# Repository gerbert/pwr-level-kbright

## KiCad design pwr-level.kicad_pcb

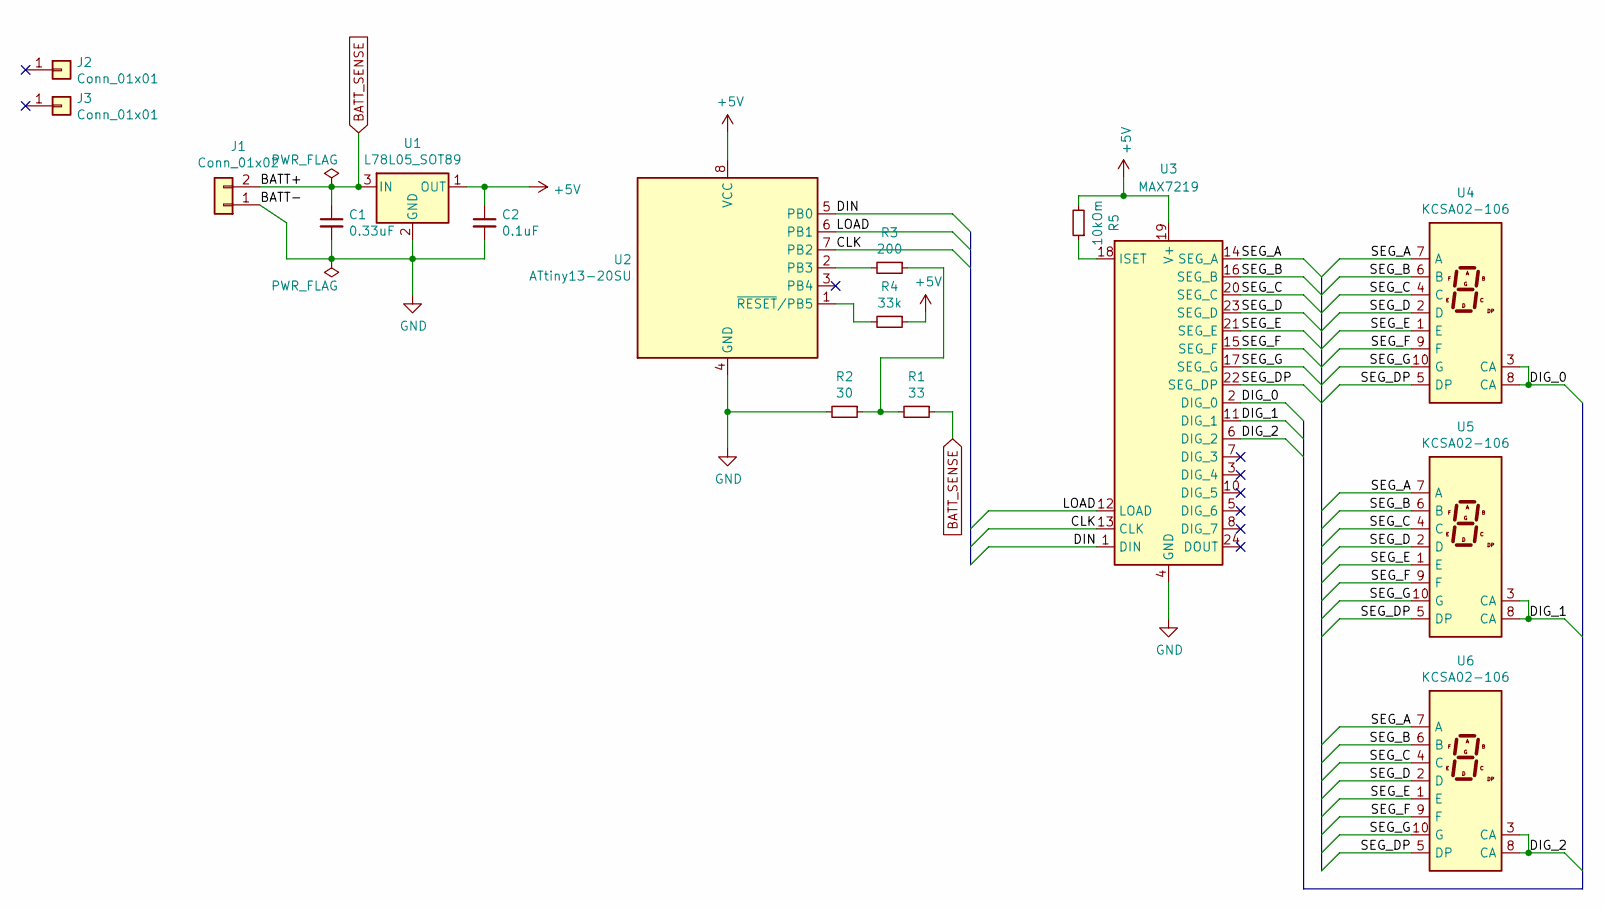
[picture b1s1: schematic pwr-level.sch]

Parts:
C1: 0.33uF; C_1206_3216Metric
C2: 0.1uF; C_1206_3216Metric
J1: Conn_01x02; SolderWirePad_1x02_P3.81mm_Drill0.8mm
J2, J3: Conn_01x01; MountingHole_4.3mm_M4
R1: 33; R_1206_3216Metric
R2: 30; R_1206_3216Metric
R3: 200; R_1206_3216Metric
R4: 33k; R_1206_3216Metric
R5: 10kOm; R_1206_3216Metric
U1: L78L05_SOT89; SOT-89-3
U2: ATtiny13-20SU; SOIJ-8_5.3x5.3mm_P1.27mm
U3: MAX7219; SOIC-24W_7.5x15.4mm_P1.27mm
U4, U5, U6: KCSA02-106; KCSC02-106

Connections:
+5V: C2.1, R4.1, R5.2, U1.1 (OUT), U2.8 (VCC), U3.19 (V+)
/CLK: U2.7 (PB2), U3.13 (CLK)
/DIG_0: U3.2 (DIG_0), U4.3 (CA), U4.8 (CA)
/DIG_1: U3.11 (DIG_1), U5.3 (CA), U5.8 (CA)
/DIG_2: U3.6 (DIG_2), U6.3 (CA), U6.8 (CA)
/DIN: U2.5 (PB0), U3.1 (DIN)
/LOAD: U2.6 (PB1), U3.12 (LOAD)
/SEG_A: U3.14 (SEG_A), U4.7 (A), U5.7 (A), U6.7 (A)
/SEG_B: U3.16 (SEG_B), U4.6 (B), U5.6 (B), U6.6 (B)
/SEG_C: U3.20 (SEG_C), U4.4 (C), U5.4 (C), U6.4 (C)
/SEG_D: U3.23 (SEG_D), U4.2 (D), U5.2 (D), U6.2 (D)
/SEG_DP: U3.22 (SEG_DP), U4.5 (DP), U5.5 (DP), U6.5 (DP)
/SEG_E: U3.21 (SEG_E), U4.1 (E), U5.1 (E), U6.1 (E)
/SEG_F: U3.15 (SEG_F), U4.9 (F), U5.9 (F), U6.9 (F)
/SEG_G: U3.17 (SEG_G), U4.10 (G), U5.10 (G), U6.10 (G)
BATT_SENSE: C1.1, J1.2, R1.1, U1.3 (IN)
GND: C1.2, C2.2, J1.1, R2.2, U1.2 (GND), U2.4 (GND), U3.4 (GND), U3.9 (GND)
unnamed: R1.2, R2.1, R3.1
unnamed: R3.2, U2.2 (PB3)
unnamed: R4.2, U2.1 (~RESET~/PB5)
unnamed: R5.1, U3.18 (ISET)

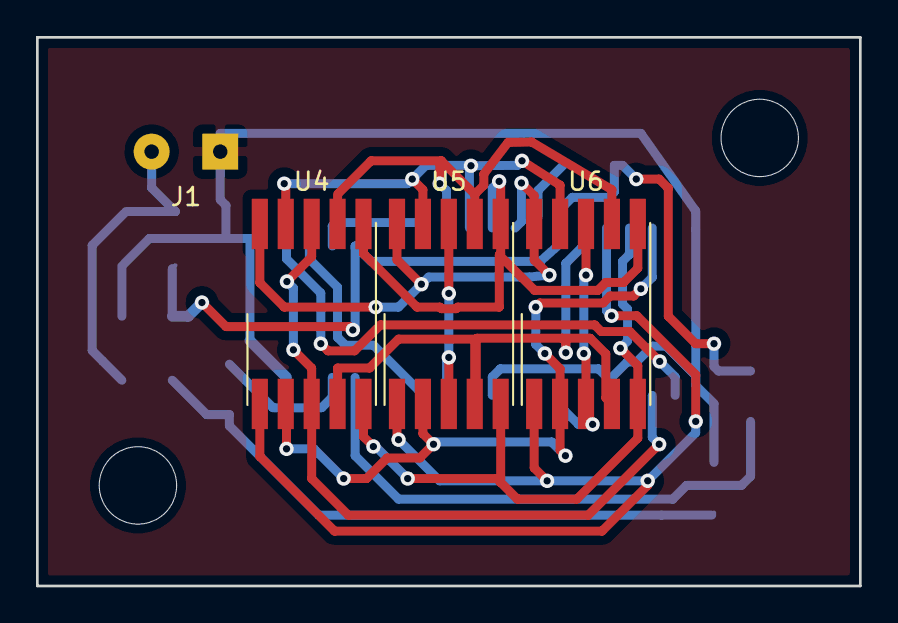
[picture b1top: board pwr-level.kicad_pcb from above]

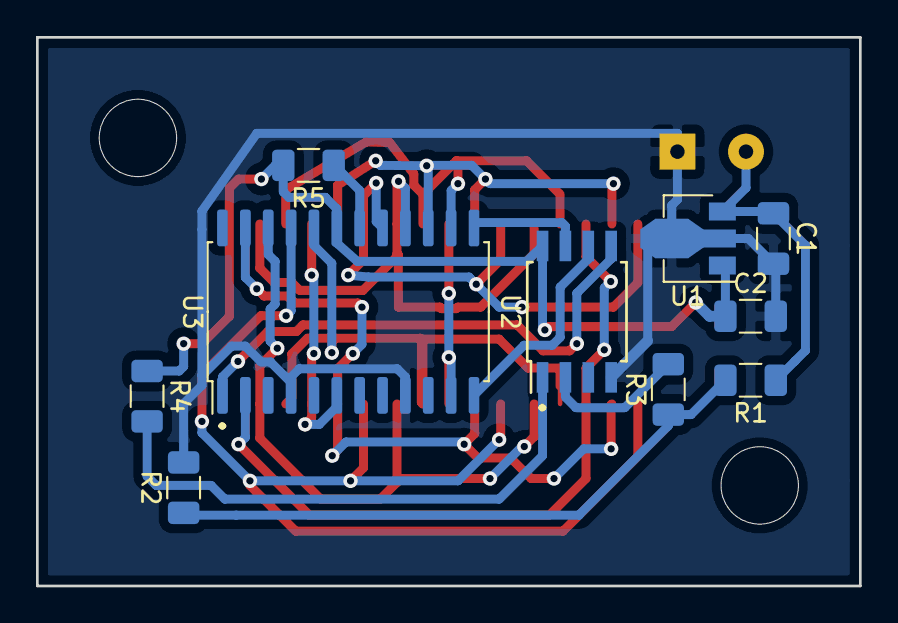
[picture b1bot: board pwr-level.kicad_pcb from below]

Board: 2 copper layers, 45.7 x 30.5 mm, 16 parts (10 on the bottom side), 21 nets.

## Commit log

2021-02-04 Schematics/PCB update
    - Added current limit resistor for LED display
    - Updated PCB layout
2021-02-04 Schematics update
    - Added 1pin markers for CPU/LED driver
    - Updated b.Cu/f.Cu GND fill
2021-02-05 Resistor devider values update for ADC
